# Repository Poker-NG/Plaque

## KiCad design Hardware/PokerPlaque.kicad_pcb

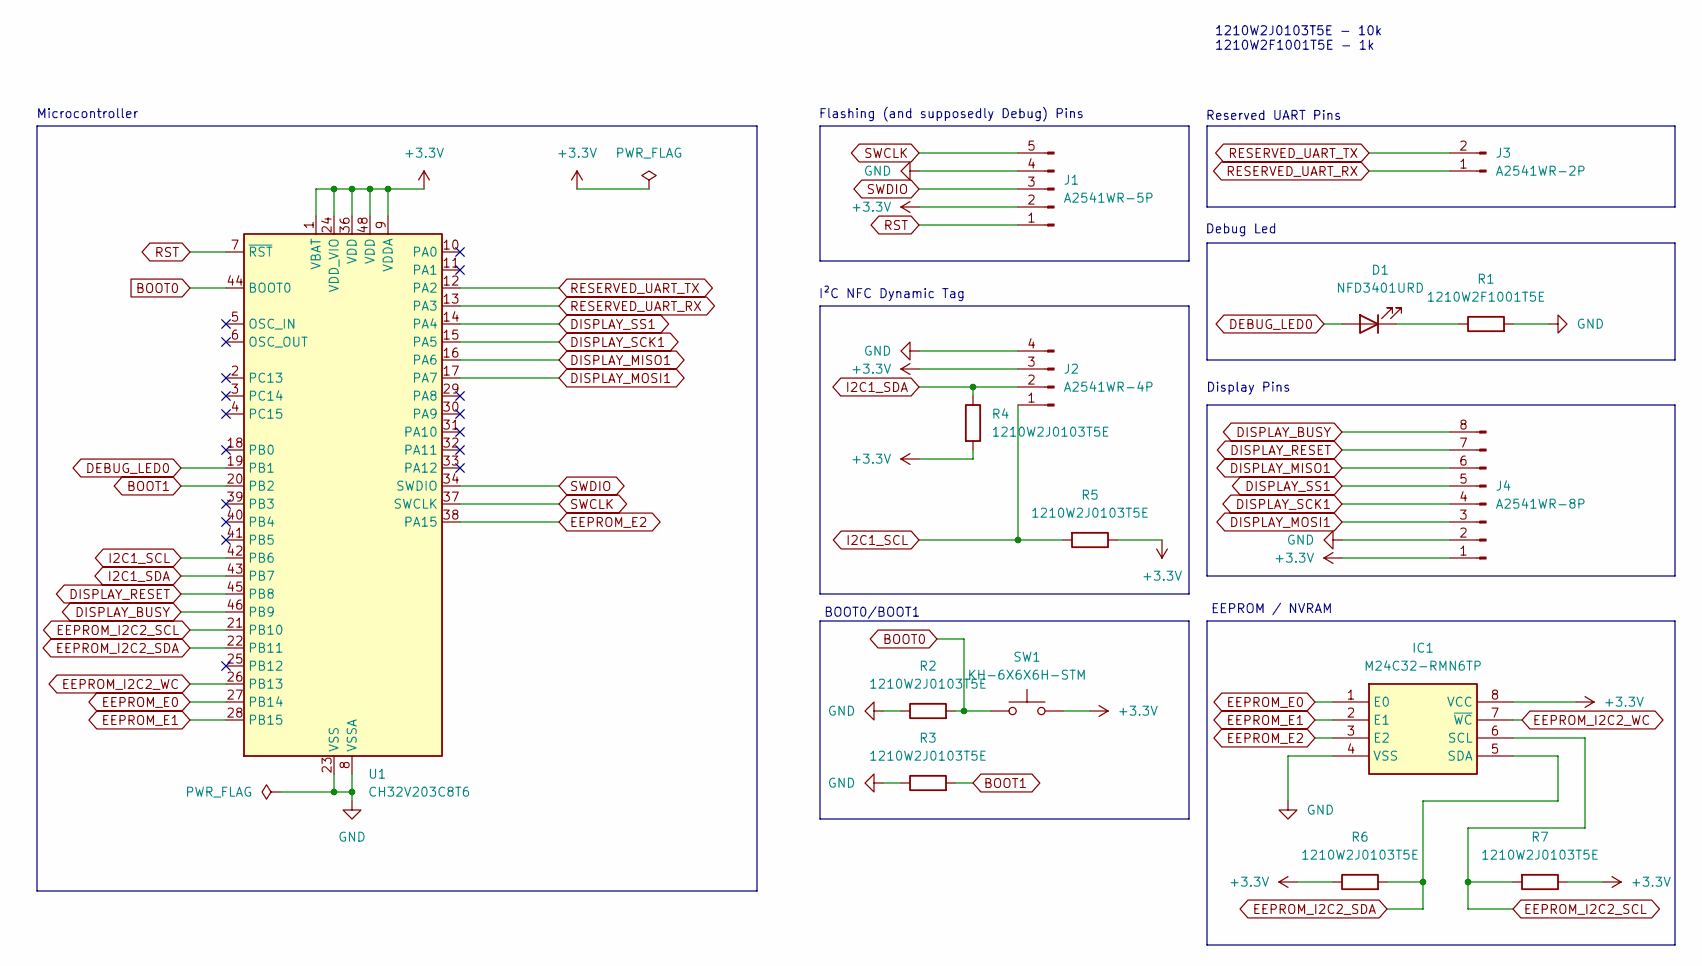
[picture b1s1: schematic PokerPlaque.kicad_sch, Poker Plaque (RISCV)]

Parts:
D1: NFD3401URD; LED_D3.0mm
IC1: M24C32-RMN6TP; SOIC127P600X175-8N; Mouser Part Number 511-M24C32-RMN6TP
J1: A2541WR-5P; PinHeader_1x05_P2.54mm_Horizontal
J2: A2541WR-4P; PinHeader_1x04_P2.54mm_Horizontal
J3: A2541WR-2P; PinHeader_1x02_P2.54mm_Horizontal
J4: A2541WR-8P; PinHeader_1x08_P2.54mm_Horizontal
R1: 1210W2F1001T5E; R_1210_3225Metric
R2, R3, R4, R5, R6, R7: 1210W2J0103T5E; R_1210_3225Metric
SW1: KH-6X6X6H-STM; SW_Push_1P1T_NO_6x6mm_H9.5mm
U1: CH32V203C8T6; LQFP-48_7x7mm_P0.5mm

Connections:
+3.3V: IC1.8 (VCC), J1.2, J2.3, J4.1, R4.2, R5.1, R6.1, R7.1, SW1.2, U1.1 (VBAT), U1.9 (VDDA), U1.24 (VDD_VIO), U1.36 (VDD), U1.48 (VDD)
BOOT0: R2.2, SW1.1, U1.44 (BOOT0)
BOOT1: R3.2, U1.20 (PB2)
DEBUG_LED0: D1.2 (A), U1.19 (PB1)
DISPLAY_BUSY: J4.8, U1.46 (PB9)
DISPLAY_MISO1: J4.6, U1.16 (PA6)
DISPLAY_MOSI1: J4.3, U1.17 (PA7)
DISPLAY_RESET: J4.7, U1.45 (PB8)
DISPLAY_SCK1: J4.4, U1.15 (PA5)
DISPLAY_SS1: J4.5, U1.14 (PA4)
EEPROM_E0: IC1.1 (E0), U1.27 (PB14)
EEPROM_E1: IC1.2 (E1), U1.28 (PB15)
EEPROM_E2: IC1.3 (E2), U1.38 (PA15)
EEPROM_I2C2_SCL: IC1.6 (SCL), R7.2, U1.21 (PB10)
EEPROM_I2C2_SDA: IC1.5 (SDA), R6.2, U1.22 (PB11)
EEPROM_I2C2_WC: IC1.7 (~WC), U1.26 (PB13)
GND: IC1.4 (VSS), J1.4, J2.4, J4.2, R1.2, R2.1, R3.1, U1.8 (VSSA), U1.23 (VSS), U1.35 (VSS), U1.47 (VSS)
I2C1_SCL: J2.1, R5.2, U1.42 (PB6)
I2C1_SDA: J2.2, R4.1, U1.43 (PB7)
unnamed: D1.1 (K), R1.1
RESERVED_UART_RX: J3.1, U1.13 (PA3)
RESERVED_UART_TX: J3.2, U1.12 (PA2)
RST: J1.1, U1.7 (~RST)
SWCLK: J1.5, U1.37 (SWCLK)
SWDIO: J1.3, U1.34 (SWDIO)

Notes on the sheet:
1210W2J0103T5E - 10k 1210W2F1001T5E - 1k
Display Pins
Flashing (and supposedly Debug) Pins
I²C NFC Dynamic Tag
Microcontroller
Debug Led
BOOT0/BOOT1
Reserved UART Pins
EEPROM / NVRAM

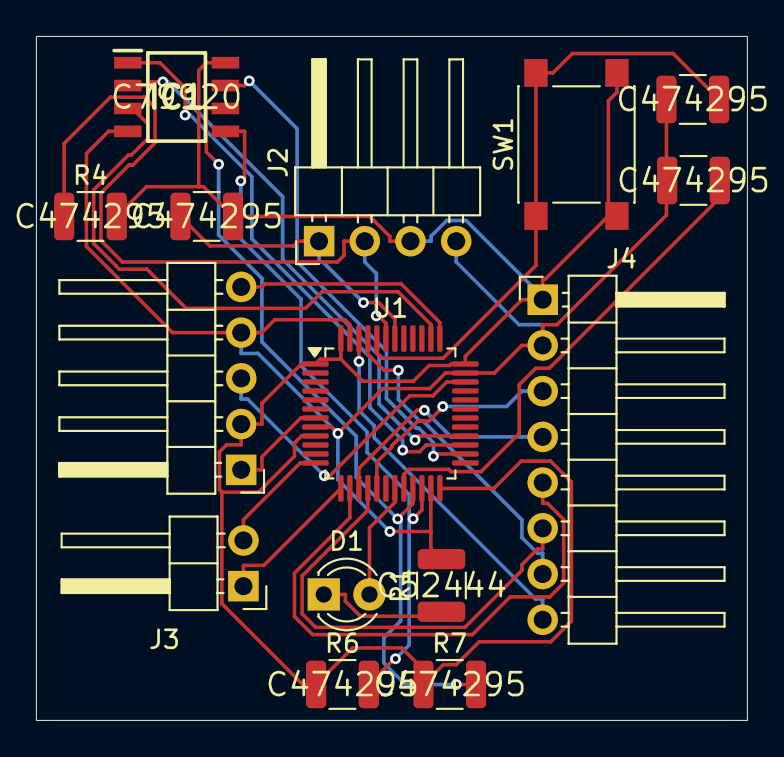
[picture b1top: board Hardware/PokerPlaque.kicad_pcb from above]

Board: 2 copper layers, 39.5 x 38.0 mm, 15 parts (0 on the bottom side), 25 nets.

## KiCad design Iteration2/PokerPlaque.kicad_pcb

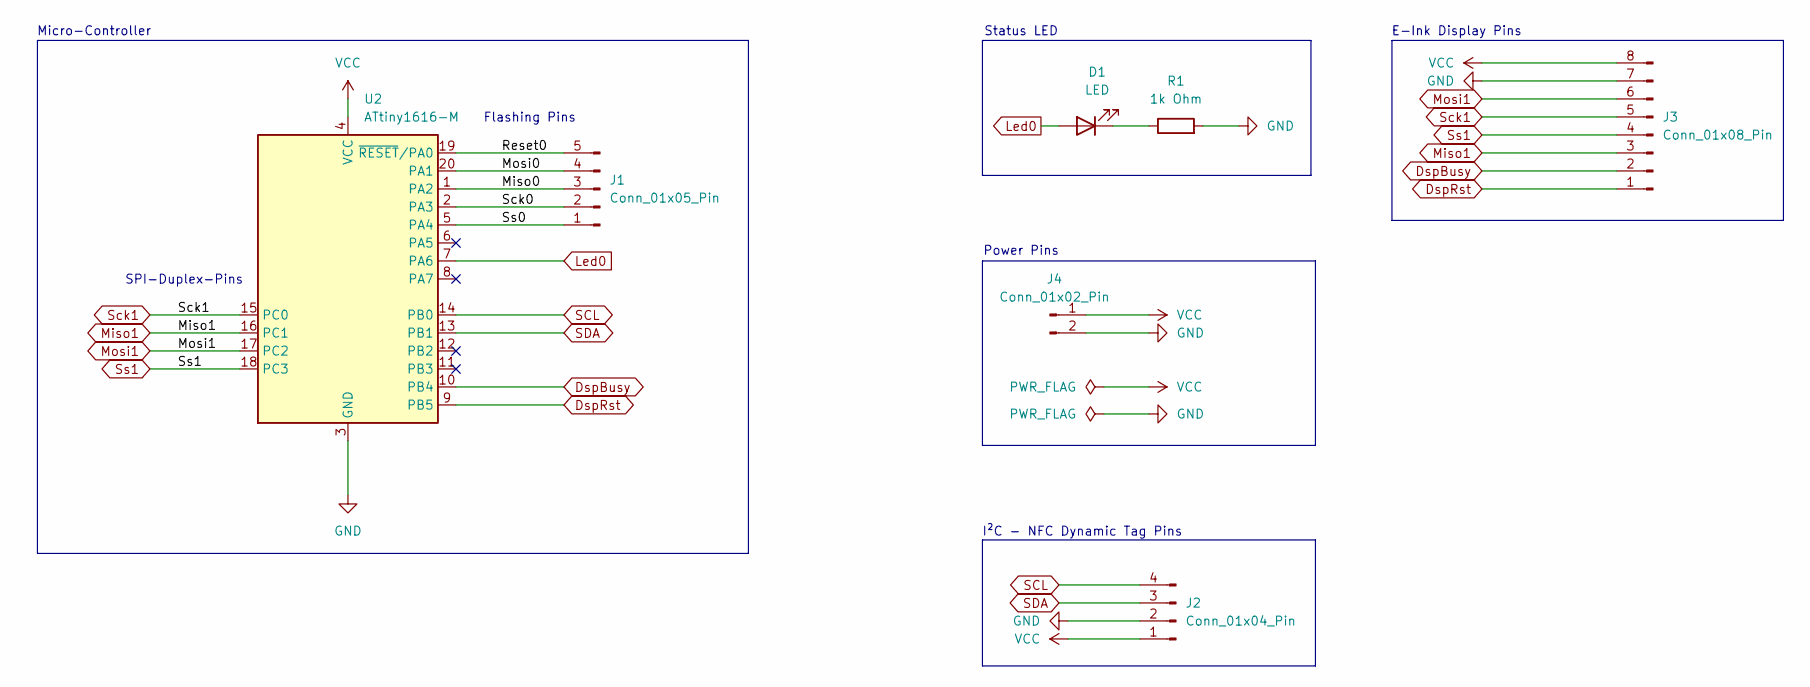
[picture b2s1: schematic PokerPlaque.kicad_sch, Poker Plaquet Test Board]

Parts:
D1: LED; LED_D4.0mm
J1: Conn_01x05_Pin; PinHeader_1x05_P2.54mm_Horizontal
J2: Conn_01x04_Pin; PinHeader_1x04_P2.54mm_Horizontal
J3: Conn_01x08_Pin; PinHeader_1x08_P2.54mm_Horizontal
J4: Conn_01x02_Pin; PinHeader_1x02_P2.54mm_Horizontal
R1: 1k Ohm; R_2010_5025Metric
U2: ATtiny1616-M; VQFN-20-1EP_3x3mm_P0.4mm_EP1.7x1.7mm

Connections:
/Miso0: J1.3, U2.1 (PA2)
/Mosi0: J1.4, U2.20 (PA1)
/Reset0: J1.5, U2.19 (~RESET/PA0)
/Sck0: J1.2, U2.2 (PA3)
/Ss0: J1.1, U2.5 (PA4)
DspBusy: J3.2, U2.10 (PB4)
DspRst: J3.1, U2.9 (PB5)
GND: J2.2, J3.7, J4.2, R1.2, U2.3 (GND), U2.21 (GND)
Led0: D1.2 (A), U2.7 (PA6)
Miso1: J3.3, U2.16 (PC1)
Mosi1: J3.6, U2.17 (PC2)
unnamed: D1.1 (K), R1.1
SCL: J2.4, U2.14 (PB0)
SDA: J2.3, U2.13 (PB1)
Sck1: J3.5, U2.15 (PC0)
Ss1: J3.4, U2.18 (PC3)
VCC: J2.1, J3.8, J4.1, U2.4 (VCC)

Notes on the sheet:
Flashing Pins
I²C - NFC Dynamic Tag Pins
E-Ink Display Pins
SPI-Duplex-Pins
Power Pins
Micro-Controller
Status LED

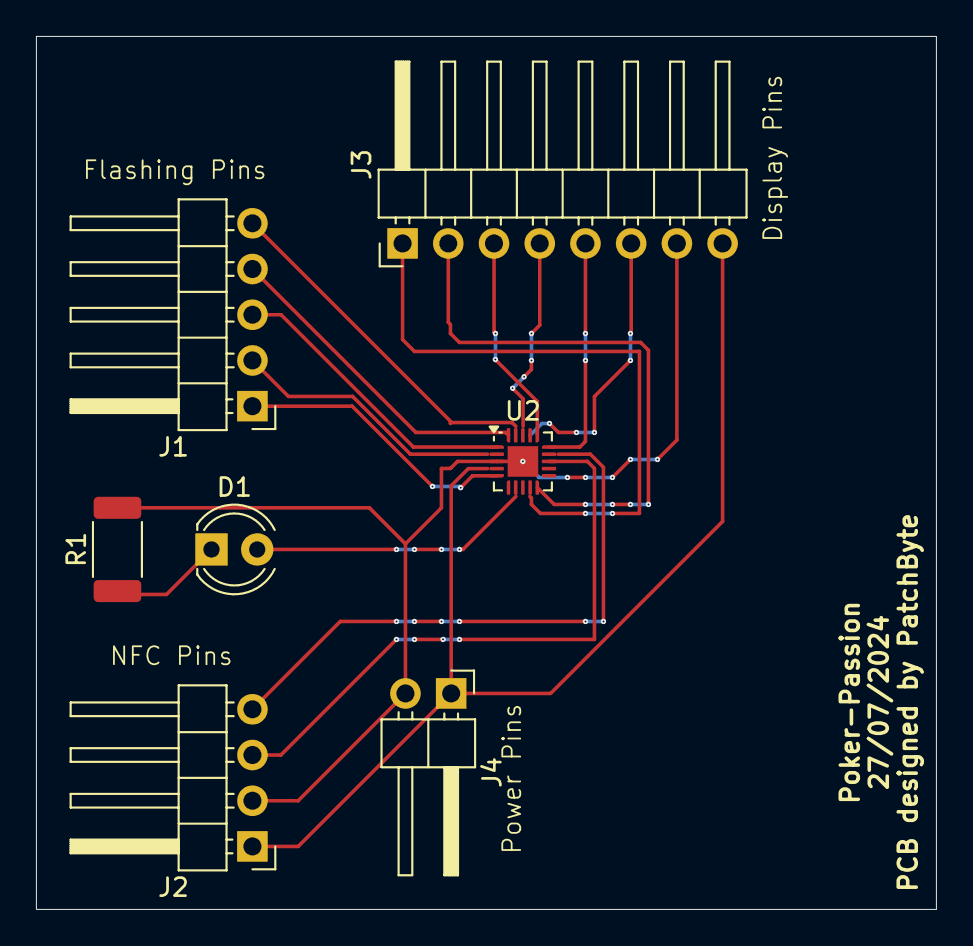
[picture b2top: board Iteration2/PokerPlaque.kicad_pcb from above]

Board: 2 copper layers, 50.0 x 48.5 mm, 7 parts (0 on the bottom side), 17 nets.

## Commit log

2024-07-31 Added second iteration, needs to be redone asap
2024-07-31 Renamed files
2024-07-31 I f-ed the whole pcb, here is my rework, rip 50 euros
2024-07-31 Designed pcb
2024-07-31 Added labeling
2024-08-01 Increased Via Size
2024-08-01 Reworked tracks and vias
2024-08-01 Replaced micro vias with normal vias
2024-09-16 feat: new riscv design
2024-09-16 feat: added some necessities
2024-09-16 feat: changed some things
2024-09-16 feat: revamped
2024-09-19 feat: more things
2024-10-05 feat: developed base firmware and tests for plaque
2024-10-05 Create LICENSE
2024-10-05 chore: revisioning debug logs
2024-10-09 feat: added debug led tests
2024-10-09 feat: rng
2024-10-11 chore: moving tests to actual tests
